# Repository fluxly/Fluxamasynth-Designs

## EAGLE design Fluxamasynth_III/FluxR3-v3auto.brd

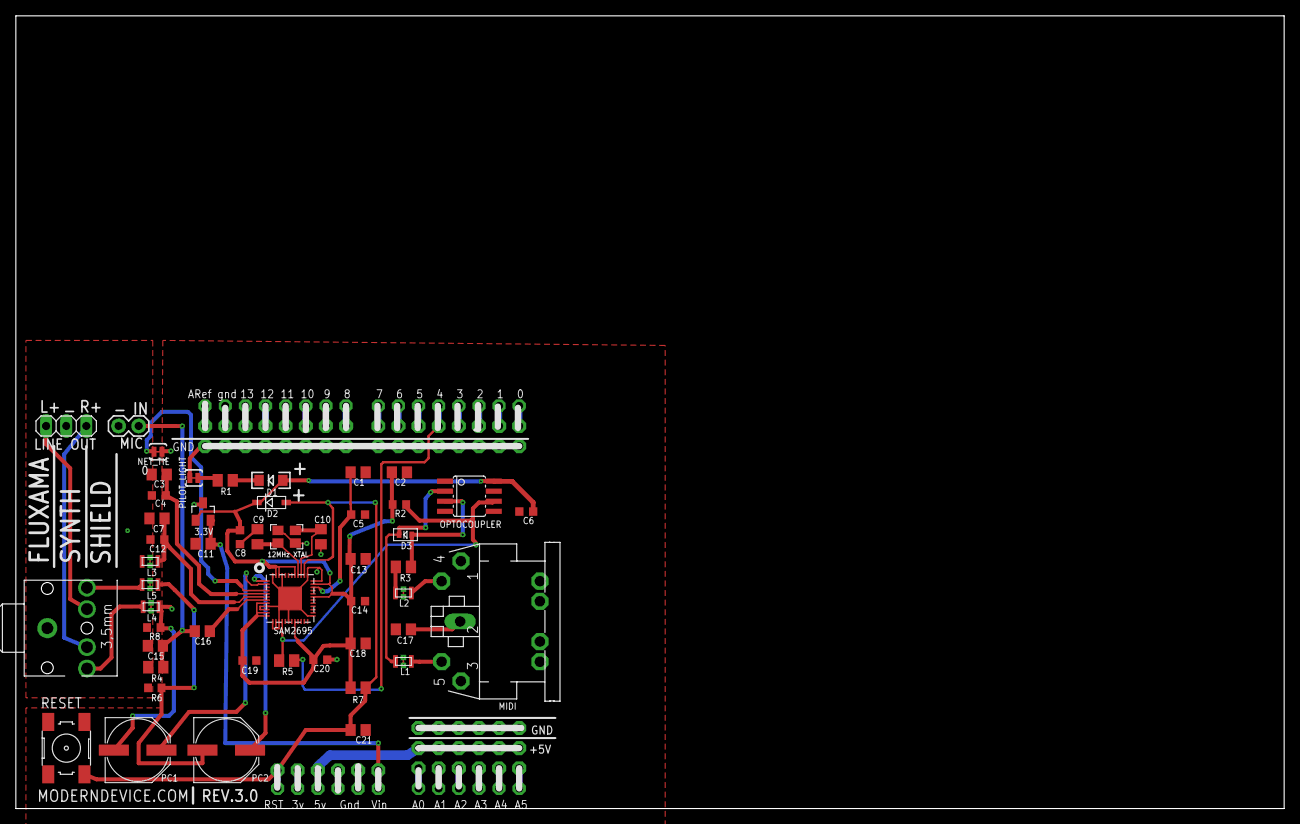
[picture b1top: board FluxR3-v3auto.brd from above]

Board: 2 copper layers, 160.0 x 100.0 mm, 59 parts (0 on the bottom side), 52 nets.

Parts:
3.3V: 3.3V; SOT23
ARDUINO: ARDUINO-NOHOLE
C1, C3, C7, C11, C13, C18: 10uf; C0805
C2, C17: .1uf; C0805
C4, C5, C6, C8, C12, C14, C19, C20: .1uf; C0603K
C9, C10: 22pf; C0805
C15: 220pf; C0805
C16: 1uf; C0805
C21: 1uF; C0805
D1: LED-1206
D2: SOD-123
D3: SOD-523
JACK: STEREOJACK; STX3100
L1, L2, L3, L4, L5: NFM21CC223R1H3D; 3PC
LINEOUT: 1X03
MIC_JACK: 1X02
MIDI: MIDIJACK; CP-2350
NET_TIE: MODERNDEVICE_SOLDERJUMPERTRACE; MODERNDEVICE_SJ_2S-TRACE
OPTOCOUPLER: HCPL0500; SOIC08
PC1, PC2: 100u; PANASONIC_E
PILOT_LIGHT: MODERNDEVICE_SOLDERJUMPERTRACE; MODERNDEVICE_SJ_2S-TRACE
Q1: CX3225GB12000P0HPQCC, 253-1168-1-ND; MODERNDEVICE_NX3225
R1: 1K; M0805
R2: 4.7k; R0603
R3, R5: 220; M0805
R4: 4.7k; M0805
R6, R8: 47k; R0603
R7: 10k; M0805
RESET: 6MM_SWITCH
SAM2695: SAM2695; QFN48
U$1, U$2, U$3, U$4: 1X8_CLEAN
U$10, U$11, U$12, U$13: 1X6_CLEAN

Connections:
+3V3: 3.3V.1, C2.1, C6.1, C8.1, C13.1, C14.1, C18.1, C19.1, C20.1, D1.A, D2.C, OPTOCOUPLER.8, R2.1, R7.2, SAM2695.8, SAM2695.11, SAM2695.12, SAM2695.20, SAM2695.31, SAM2695.35, SAM2695.41, SAM2695.46, SAM2695.47
+5V: ARDUINO.5V, U$11.P$1, U$11.P$2, U$11.P$3, U$11.P$4, U$11.P$5, U$11.P$6, U$12.P$4
A0: ARDUINO.A0, U$13.P$6
A1: ARDUINO.A1, U$13.P$5
A2: ARDUINO.A2, U$13.P$4
A3: ARDUINO.A3, U$13.P$3
A4: ARDUINO.A4, U$13.P$2
A5: ARDUINO.A5, U$13.P$1
AGND: C3.2, C4.2, C7.2, C12.2, C15.2, JACK.1, L3.2A, L3.2B, L4.2A, L4.2B, L5.2A, L5.2B, LINEOUT.2, MIC_JACK.1, NET_TIE.2, R4.1, R6.1, R8.1, SAM2695.4
AOUTL: PC2.+, SAM2695.1
AOUTR: PC1.+, SAM2695.2
GND: 3.3V.3, ARDUINO.GND, ARDUINO.GND1, ARDUINO.GND2, C1.2, C2.2, C5.2, C6.2, C8.2, C9.2, C10.2, C11.2, C13.2, C14.2, C17.2, C18.2, C19.2, C20.2, C21.2, L1.2A, L1.2B, L2.2A, L2.2B, NET_TIE.1, OPTOCOUPLER.5, PILOT_LIGHT.1, Q1.2, Q1.4, RESET.1, SAM2695.9, SAM2695.10, SAM2695.13, SAM2695.14, SAM2695.15, SAM2695.18, SAM2695.25, SAM2695.36, SAM2695.37, SAM2695.45, SAM2695.48, SAM2695.EXP, U$1.P$2, U$3.P$1, U$3.P$2, U$3.P$3, U$3.P$4, U$3.P$5, U$3.P$6, U$3.P$7, U$3.P$8, U$4.P$1, U$4.P$2, U$4.P$3, U$4.P$4, U$4.P$5, U$4.P$6, U$4.P$7, U$4.P$8, U$10.P$1, U$10.P$2, U$10.P$3, U$10.P$4, U$10.P$5, U$10.P$6, U$12.P$2, U$12.P$3
MICIN: C16.1, SAM2695.7
MICROPHONE: C15.1, C16.2, MIC_JACK.2, R4.2
MIDI_FROM_ARDUINO: ARDUINO.D4, R5.1, U$2.P$4
MIDI_IN: OPTOCOUPLER.6, R2.2, R5.2, SAM2695.16
unnamed: ARDUINO.D1, U$2.P$7
unnamed: L2.1, MIDI.4
unnamed: ARDUINO.3V, U$12.P$5
unnamed: L5.1, PC2.-, R6.2
unnamed: JACK.5, L4.3
unnamed: L2.3, R3.2
unnamed: D3.K, L1.3, OPTOCOUPLER.2
unnamed: D1.C, R1.2
unnamed: C17.1, MIDI.2
unnamed: L1.1, MIDI.5
unnamed: D3.A, OPTOCOUPLER.3, R3.1
unnamed: ARDUINO.D8, U$1.P$8
unnamed: ARDUINO.D9, U$1.P$7
unnamed: JACK.4, LINEOUT.3
unnamed: ARDUINO.D11, U$1.P$5
unnamed: ARDUINO.D10, U$1.P$6
unnamed: JACK.3, LINEOUT.1
unnamed: ARDUINO.D12, U$1.P$4
unnamed: ARDUINO.D13, U$1.P$3
unnamed: ARDUINO.D6, U$2.P$2
unnamed: ARDUINO.AREF, U$1.P$1
unnamed: ARDUINO.D5, U$2.P$3
unnamed: ARDUINO.D0, U$2.P$8
unnamed: ARDUINO.D2, U$2.P$6
unnamed: ARDUINO.D3, U$2.P$5
unnamed: ARDUINO.D7, U$2.P$1
unnamed: PILOT_LIGHT.2, R1.1
OUTVC12: C1.1, C5.1, SAM2695.34
OUT_L: JACK.2, L5.3
OUT_R: L4.1, PC1.-, R8.2
RST: ARDUINO.RESET, C21.1, D2.A, R7.1, RESET.3, SAM2695.38, U$12.P$6
VA33: C7.1, C12.1, L3.1, SAM2695.6
VCM: C3.1, C4.1, SAM2695.5
VIN: 3.3V.2, ARDUINO.VIN, C11.1, U$12.P$1
XTL1: C10.1, Q1.3, SAM2695.39
XTL2: C9.1, Q1.1, SAM2695.40

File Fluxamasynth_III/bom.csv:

| Part                        | Value                               | Device                         | Package                  | Description                                                      |
|-----------------------------+-------------------------------------+--------------------------------+--------------------------+------------------------------------------------------------------|
| 3.3V                        | 3.3V                                | REGULATORSOT23                 | SOT23                    |                                                                  |
| C1,C3,C7,C11,C13,C18        | 10uf                                | C-USC0805                      | C0805                    | CAPACITOR, American symbol                                       |
| C2,C17,C21                  | .1uf                                | C-USC0805                      | C0805                    | CAPACITOR, American symbol                                       |
| C4,C5,C6,C8,C12,C14,C19,C20 | .1uf                                | C-USC0603K                     | C0603K                   | CAPACITOR, American symbol                                       |
| C9,C10                      | 22pf                                | C-USC0805                      | C0805                    | CAPACITOR, American symbol                                       |
| C15                         | 220pf                               | C-USC0805                      | C0805                    | CAPACITOR, American symbol                                       |
| C16                         | 1uf                                 | C-USC0805                      | C0805                    | CAPACITOR, American symbol                                       |
| C18                         | 10uf                                | C-USC0805                      | C0805                    | CAPACITOR, American symbol                                       |
| D1                          |                                     | LED1206                        | LED-1206                 | LEDs                                                             |
| D2,D3                       |                                     | DIODE_SOD-123                  | SOD-123                  | Diode                                                            |
| JACK                        | STEREOJACK                          | STEREOJACK                     | STX3100                  | MIC/HEADPHONE JACK                                               |
| L1,L2,L3,L4,L5              | NFM21CC223R1H3D                     | NFM21CC223R1H3D                | 3PC                      | CAPACITOR-TYPE NOISE SUPPRESSION FILTER digikey #NFM21CC223R1H3D |
| MIC_JACK                    |                                     | M02PTH                         | 1X02                     | Header 2                                                         |
| MIDI_JACK                   | MIDIJACK                            | MIDIJACK                       | CP-2350                  | DIN 5 jack also known as MIDI jack                               |
| OPTOCOUPLER                 | HCPL0500                            | HCPL0500                       | SOIC08                   | HEWLETT PACKARD OPTO COUPLER                                     |
| PC1,PC2                     | 100u                                | CPOL-USE                       | PANASONIC_E              | POLARIZED CAPACITOR, American symbol                             |
| Q1                          | CX3225GB12000P0HPQCC, 253-1168-1-ND | MODERNDEVICE_XTAL-4-3225       | MODERNDEVICE_NX3225      | Classic 4-pin 3.2 x 2.5mm crystal                                |
| R1                          | 1K                                  | R-US_R0603                     | R0603                    | RESISTOR, American symbol                                        |
| R2,R4                       | 4.7k                                | R-US_R0603                     | R0603                    | RESISTOR, American symbol                                        |
| R3,R5                       | 220                                 | R-US_R0603                     | R0603                    | RESISTOR, American symbol                                        |
| R6,R8                       | 47k                                 | R-US_R0603                     | R0603                    | RESISTOR, American symbol                                        |
| R7                          | 100k                                | R-US_R0603                     | R0603                    | RESISTOR, American symbol                                        |
| RESET                       |                                     | 6MM_SWITCH6MM_SWITCH           | 6MM_SWITCH               | OMRON SWITCH                                                     |
| SAM2695                     | SAM2695                             | SAM2695                        | QFN48                    |                                                                  |

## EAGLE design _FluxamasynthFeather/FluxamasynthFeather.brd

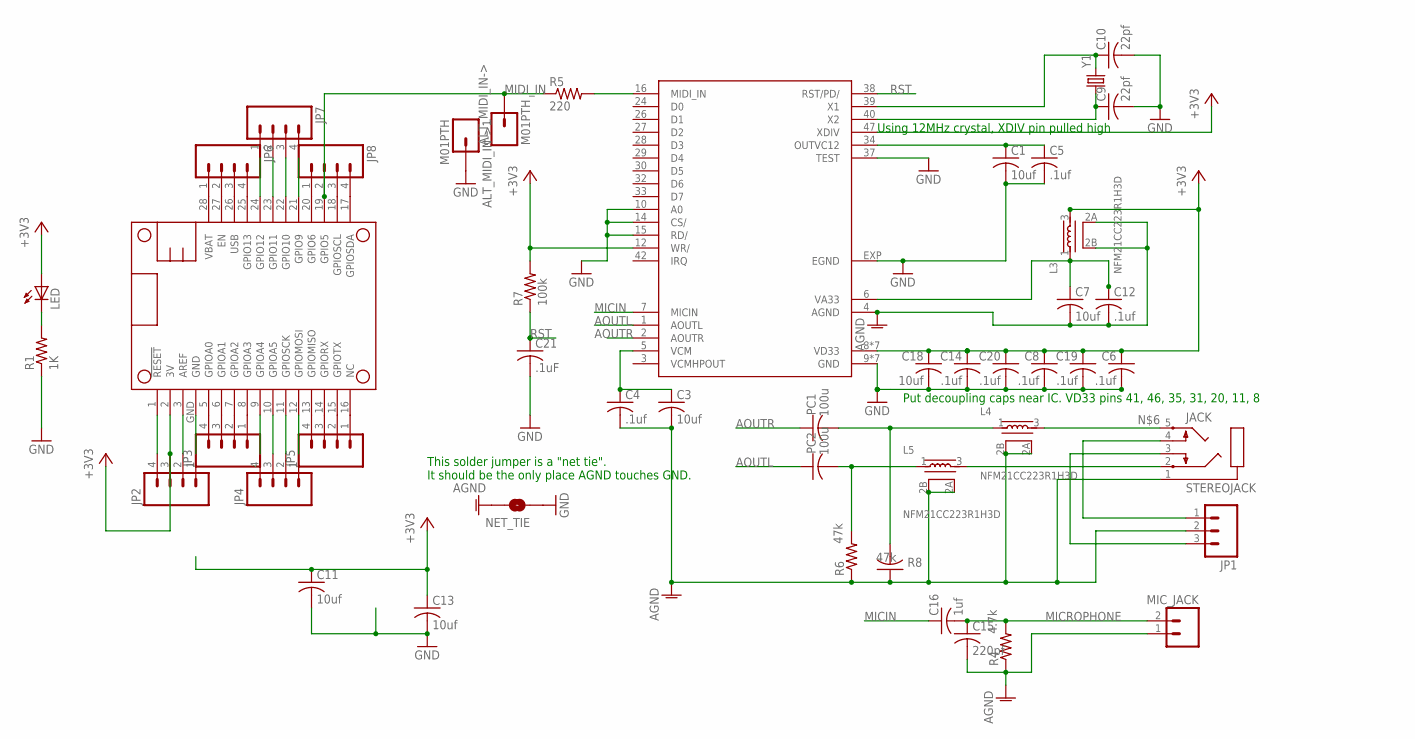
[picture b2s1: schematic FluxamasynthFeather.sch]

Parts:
ALT_MIDI_IN->, ALT_MIDI_IN->1: M01PTH; 1X01
C1, C3, C7, C11, C13: 10uf; C0805K
C4, C5, C6, C8, C12, C14, C19, C20: .1uf; C0603K
C9, C10: 22pf; C0603
C15: 220pf; C0805K
C16: 1uf; C0603K
C18: 10uf; C0603K
C21: .1uF; C0603K
JACK: STEREOJACK; STX3100
JP1: M03PTH; 1X03
JP2, JP3, JP4, JP5, JP6, JP7, JP8: M041X04_NO_SILK; 1X04_NO_SILK
L3, L4, L5: NFM21CC223R1H3D; 3PC
LED: LED0603; LED-0603
MIC_JACK: M02PTH; 1X02
MS1: FEATHERWING
NET_TIE: MODERNDEVICE_SOLDERJUMPERTRACE; MODERNDEVICE_SJ_2S-TRACE
PC1, PC2: 100u; C1206K
R1: 1K; R0603
R4: 4.7k; R0603
R5: 220; R0603
R6: 47k; R0603
R7: 100k; R0603
R8: 47k; C0603K
SAM2695: SAM2695; QFN48
Y1: CRYSTALTXC-7A; CRYSTAL-TXC-7A

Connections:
+3V3: C6.1, C8.1, C11.1, C13.1, C14.1, C18.1, C19.1, C20.1, JP2.3, L3.3, LED.A, MS1.2 (3V), R7.2, SAM2695.8 (VD33), SAM2695.11 (VD33), SAM2695.12 (WR/), SAM2695.20 (VD33), SAM2695.31 (VD33), SAM2695.35 (VD33), SAM2695.41 (VD33), SAM2695.46 (VD33), SAM2695.47 (XDIV)
AGND: C3.2, C4.2, C7.2, C12.2, C15.2, JACK.1, JP1.2, L3.2A, L3.2B, L4.2A, L4.2B, L5.2A, L5.2B, MIC_JACK.1, NET_TIE.2, R4.1, R6.1, R8.1, SAM2695.4 (AGND)
AOUTL: PC2.1, SAM2695.1 (AOUTL)
AOUTR: PC1.1, SAM2695.2 (AOUTR)
GND: ALT_MIDI_IN->1.1, C1.2, C5.2, C6.2, C8.2, C9.2, C10.2, C11.2, C13.2, C14.2, C18.2, C19.2, C20.2, C21.2, NET_TIE.1, R1.1, SAM2695.9 (GND), SAM2695.10 (A0), SAM2695.13 (GND), SAM2695.14 (CS/), SAM2695.15 (RD/), SAM2695.18 (GND), SAM2695.25 (GND), SAM2695.36 (GND), SAM2695.37 (TEST), SAM2695.45 (GND), SAM2695.48 (GND), SAM2695.EXP (EGND)
MICIN: C16.1, SAM2695.7 (MICIN)
MICROPHONE: C15.1, C16.2, MIC_JACK.2, R4.2
MIDI_IN: ALT_MIDI_IN->.1, JP8.2, MS1.19 (GPIO5), R5.1
unnamed: JP2.1, MS1.GND
unnamed: JP2.2, MS1.3 (AREF)
unnamed: JP2.4, MS1.1 (!RESET)
unnamed: JP3.1, MS1.8 (GPIOA3)
unnamed: L5.1, PC2.2, R6.2
unnamed: JACK.5, L4.3
unnamed: JP3.2, MS1.7 (GPIOA2)
unnamed: JP3.3, MS1.6 (GPIOA1)
unnamed: LED.C, R1.2
unnamed: JP3.4, MS1.5 (GPIOA0)
unnamed: JP4.1, MS1.12 (GPIOMOSI)
unnamed: R5.2, SAM2695.16 (MIDI_IN)
unnamed: JP4.2, MS1.11 (GPIOSCK)
unnamed: JP4.3, MS1.10 (GPIOA5)
unnamed: JP4.4, MS1.9 (GPIOA4)
unnamed: JP5.1, MS1.16 (NC)
unnamed: JP5.2, MS1.15 (GPIOTX)
unnamed: JP5.3, MS1.14 (GPIORX)
unnamed: JP5.4, MS1.13 (GPIOMISO)
unnamed: JP6.2, MS1.27 (EN)
unnamed: JACK.4, JP1.1
unnamed: JP6.4, MS1.25 (GPIO13)
unnamed: JP7.1, MS1.24 (GPIO12)
unnamed: JACK.3, JP1.3
unnamed: JP7.2, MS1.23 (GPIO11)
unnamed: JP7.3, MS1.22 (GPIO10)
unnamed: JP7.4, MS1.21 (GPIO9)
unnamed: JP8.1, MS1.20 (GPIO6)
unnamed: JP8.3, MS1.18 (GPIOSCL)
unnamed: JP8.4, MS1.17 (GPIOSDA)
OUTVC12: C1.1, C5.1, SAM2695.34 (OUTVC12)
OUT_L: JACK.2, L5.3
OUT_R: L4.1, PC1.2, R8.2
RST: C21.1, R7.1, SAM2695.38 (RST/PD/)
USB: JP6.3, MS1.26 (USB)
VA33: C7.1, C12.1, L3.1, SAM2695.6 (VA33)
VBAT: JP6.1, MS1.28 (VBAT)
VCM: C3.1, C4.1, SAM2695.5 (VCM)
XTL1: C10.1, SAM2695.39 (X1), Y1.P$2 (2)
XTL2: C9.1, SAM2695.40 (X2), Y1.P$1 (1)

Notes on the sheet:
Using 12MHz crystal, XDIV pin pulled high
Put decoupling caps near IC. VD33 pins 41, 46, 35, 31, 20, 11, 8
This solder jumper is a "net tie". It should be the only place AGND touches GND.

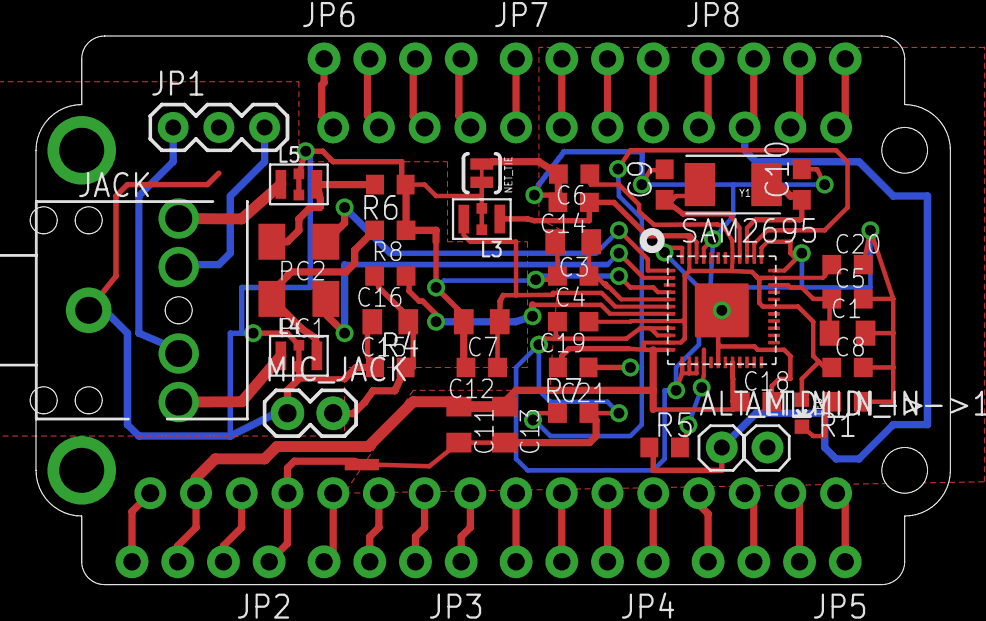
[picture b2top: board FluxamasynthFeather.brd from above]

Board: 2 copper layers, 50.8 x 30.5 mm, 47 parts (0 on the bottom side), 48 nets.

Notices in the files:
parts and their libraries:
SparkFun-FreqCtrl: Licensing: CC v3.0 Share-Alike You are welcome to use this library for commercial purposes.
